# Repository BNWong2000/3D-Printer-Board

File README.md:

# 3D-Printer-Board
A custom, 3D printer controller, intended to run Klipper. All pcb source files were made in kiCAD. This project utilizes the stock kiCAD library for basic components (Resistors, Capacitors, Diodes, Inductors, Connectors, etc), and for the main chip (STM32F407IGT6). All other components were made as a custom library. 

#### Features:
* STM32F407IGT6 32 bit MCU
* 9 Silent Stepper Drivers (Trinamic TMC 2209 with UART control)
* 8 Fan output FETs
   * Selectable Voltage for each fan using jumpers. (24V, 12V or 5v)
* 8 Heater output FETs (including 1 high power FET for heated beds and 1 high power FET for heated chamber)
* High power step down converter to 5v (max 5A)
   * This is enough to power the raspberry pi (which only needs 3A at 5v) and several fans without an external power supply
* 12v step down converter for other peripherals.
* Fused inputs and outputs.

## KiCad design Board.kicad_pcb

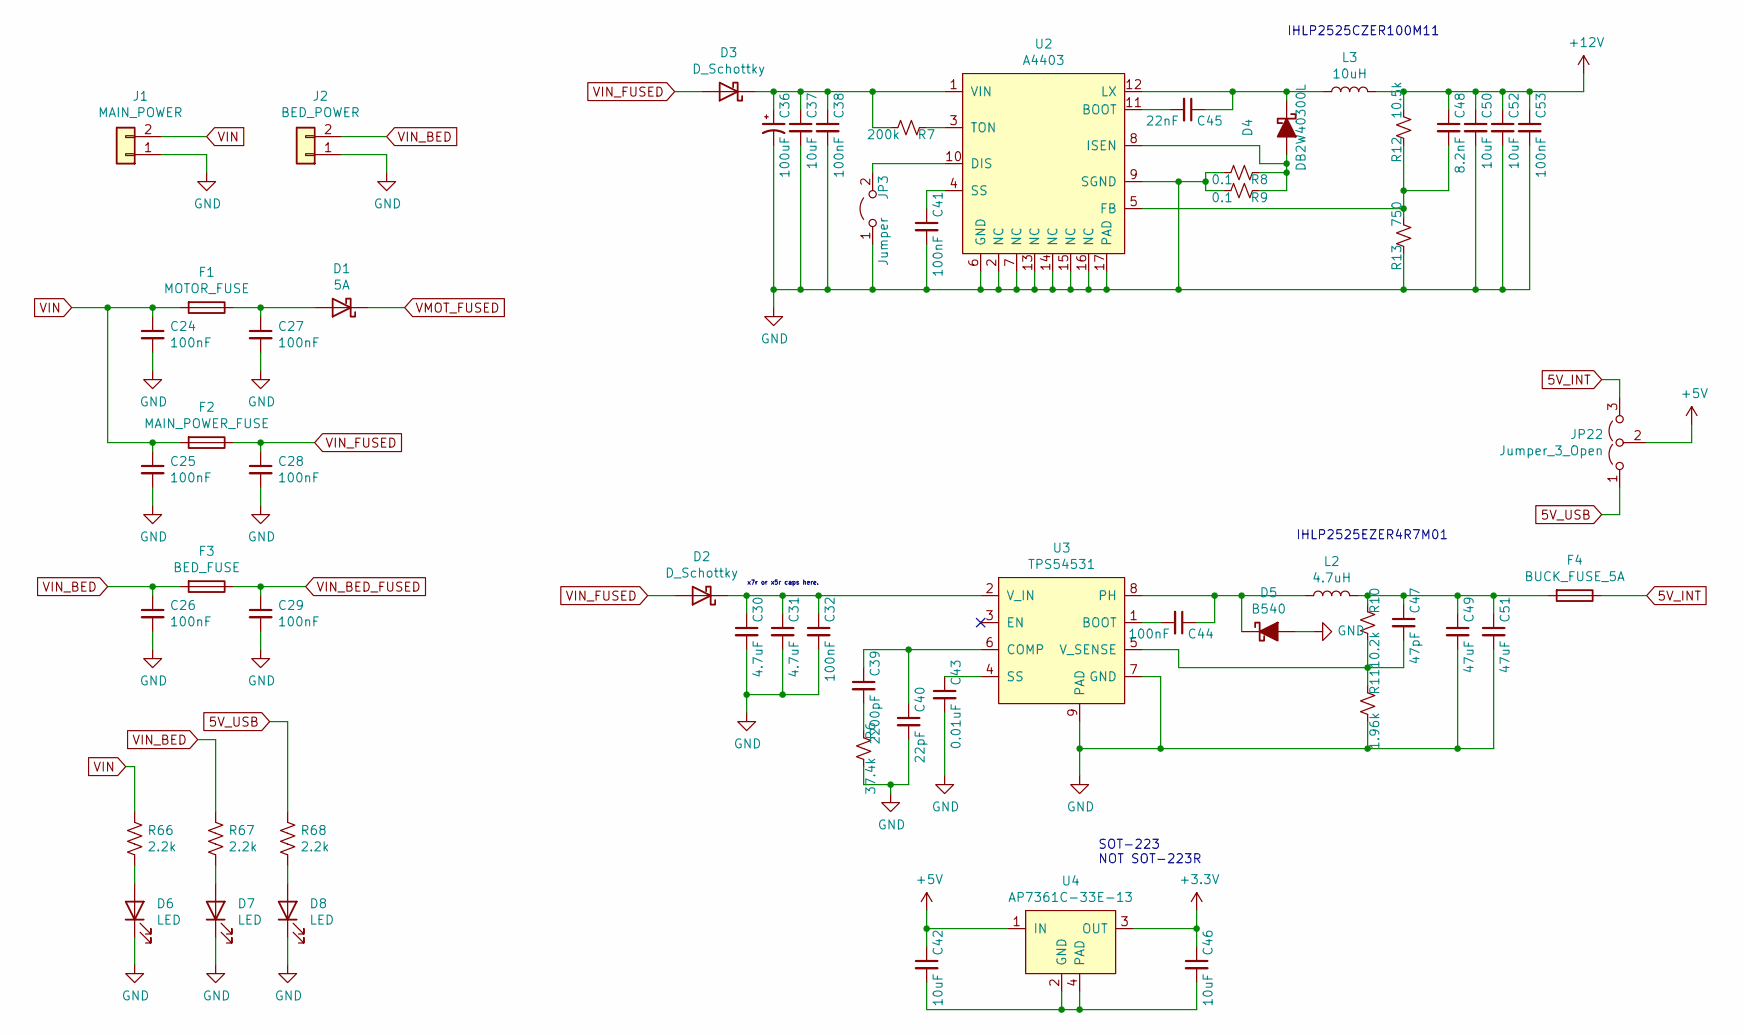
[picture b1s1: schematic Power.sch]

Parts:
C24, C25, C26, C27, C28, C29, C32, C38, C41, C44, C53: 100nF; C_0603_1608Metric_Pad1.05x0.95mm_HandSolder
C30, C31: 4.7uF; C_0805_2012Metric_Pad1.15x1.40mm_HandSolder
C36: 100uF; CP_Elec_6.3x7.7
C37, C42, C46, C50, C52: 10uF; C_0805_2012Metric_Pad1.15x1.40mm_HandSolder
C39: 2200pF; C_0603_1608Metric_Pad1.05x0.95mm_HandSolder
C40: 22pF; C_0603_1608Metric_Pad1.05x0.95mm_HandSolder
C43: 0.01uF; C_0603_1608Metric_Pad1.05x0.95mm_HandSolder
C45: 22nF; C_0603_1608Metric_Pad1.05x0.95mm_HandSolder
C47: 47pF; C_0603_1608Metric_Pad1.05x0.95mm_HandSolder
C48: 8.2nF; C_0603_1608Metric_Pad1.05x0.95mm_HandSolder
C49, C51: 47uF; C_0603_1608Metric_Pad1.05x0.95mm_HandSolder
D1: 5A; D_SMA_Handsoldering
D2, D3: D_Schottky; D_SOD-123F
D4: DB2W40300L; D_SOD-123F
D5: B540; D_SMC_Handsoldering
D6, D7, D8: LED; LED_0603_1608Metric_Pad1.05x0.95mm_HandSolder
F1: MOTOR_FUSE; Fuseholder_Blade_Mini_Keystone_3568
F2: MAIN_POWER_FUSE; Fuseholder_Blade_Mini_Keystone_3568
F3: BED_FUSE; Fuseholder_Blade_Mini_Keystone_3568
F4: BUCK_FUSE_5A; Fuseholder_Blade_Mini_Keystone_3568
J1: MAIN_POWER; TerminalBlock_Dinkle_DT-55-B01X-02_P10.00mm
J2: BED_POWER; TerminalBlock_Dinkle_DT-55-B01X-02_P10.00mm
JP3: Jumper; PinHeader_1x02_P2.54mm_Vertical
JP22: Jumper_3_Open; PinHeader_1x03_P2.54mm_Vertical
L2: 4.7uH; L_Vishay_IHLP-2525
L3: 10uH; L_Vishay_IHLP-2525
R6: 37.4k; R_0603_1608Metric_Pad1.05x0.95mm_HandSolder
R7: 200k; R_0603_1608Metric_Pad1.05x0.95mm_HandSolder
R8, R9: 0.1; R_1206_3216Metric_Pad1.42x1.75mm_HandSolder
R10: 10.2k; R_0603_1608Metric_Pad1.05x0.95mm_HandSolder
R11: 1.96k; R_0603_1608Metric_Pad1.05x0.95mm_HandSolder
R12: 10.5k; R_0603_1608Metric_Pad1.05x0.95mm_HandSolder
R13: 750; R_0603_1608Metric_Pad1.05x0.95mm_HandSolder
R66, R67, R68: 2.2k; R_0603_1608Metric_Pad1.05x0.95mm_HandSolder
U2: A4403; QFN-16-1EP_4x4mm_P0.65mm_EP2.7x2.7mm_ThermalVias
U3: TPS54531; TI_SO-PowerPAD-8_ThermalVias
U4: AP7361C-33E-13; SOT-223

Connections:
5V_INT: F4.1, JP22.3 (B)
5V_USB: JP22.1 (A), R68.1; also elsewhere on the board
+3V3: C46.1, U4.3 (OUT); also elsewhere on the board
+5V: C42.1, JP22.2 (C), U4.1 (IN); also elsewhere on the board
+12V: C48.1, C50.1, C52.1, C53.1, L3.2, R12.2; also elsewhere on the board
GND: C24.2, C25.2, C26.2, C27.2, C28.2, C29.2, C30.2, C31.2, C32.2, C36.2, C37.2, C38.2, C40.2, C41.2, C43.2, C49.2, C50.2, C51.2, C52.2, C53.2, D5.2 (A), D6.1 (K), D7.1 (K), D8.1 (K), J1.1, J2.1, JP3.1 (A), R6.2, R8.2, R9.2, R11.2, R13.1, U2.2 (NC), U2.6 (GND), U2.7 (NC), U2.9 (SGND), U2.13 (NC), U2.14 (NC), U2.15 (NC), U2.16 (NC), U2.17 (PAD), U3.7 (GND), U3.9 (PAD); also elsewhere on the board
unnamed: C27.1, D1.2 (A), F1.1
unnamed: C30.1, C31.1, C32.1, D2.1 (K), U3.2 (V_IN)
unnamed: C36.1, C37.1, C38.1, D3.1 (K), R7.2, U2.1 (VIN)
unnamed: C39.1, C40.1, U3.6 (COMP)
unnamed: C39.2, R6.1
unnamed: C41.1, U2.4 (SS)
unnamed: C42.2, C46.2, U4.2 (GND), U4.4 (PAD)
unnamed: C43.1, U3.4 (SS)
unnamed: C44.1, D5.1 (K), L2.1, U3.8 (PH)
unnamed: C44.2, U3.1 (BOOT)
unnamed: C45.1, D4.1 (K), L3.1, U2.12 (LX)
unnamed: C45.2, U2.11 (BOOT)
unnamed: C47.1, C49.1, C51.1, F4.2, L2.2, R10.1
unnamed: C47.2, R10.2, R11.1, U3.5 (V_SENSE)
unnamed: C48.2, R12.1, R13.2, U2.5 (FB)
unnamed: D4.2 (A), R8.1, R9.1, U2.8 (ISEN)
unnamed: D6.2 (A), R66.2
unnamed: D7.2 (A), R67.2
unnamed: D8.2 (A), R68.2
unnamed: JP3.2 (B), U2.10 (DIS)
unnamed: R7.1, U2.3 (TON)
VIN: C24.1, C25.1, F1.2, F2.2, J1.2, R66.1
VIN_BED: C26.1, F3.2, J2.2, R67.1
VIN_BED_FUSED: C29.1, F3.1; also elsewhere on the board
VIN_FUSED: C28.1, D2.2 (A), D3.2 (A), F2.1; also elsewhere on the board
VMOT_FUSED: D1.1 (K); also elsewhere on the board

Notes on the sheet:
x7r or x5r caps here.
IHLP2525CZER100M11
IHLP2525EZER4R7M01
SOT-223 NOT SOT-223R

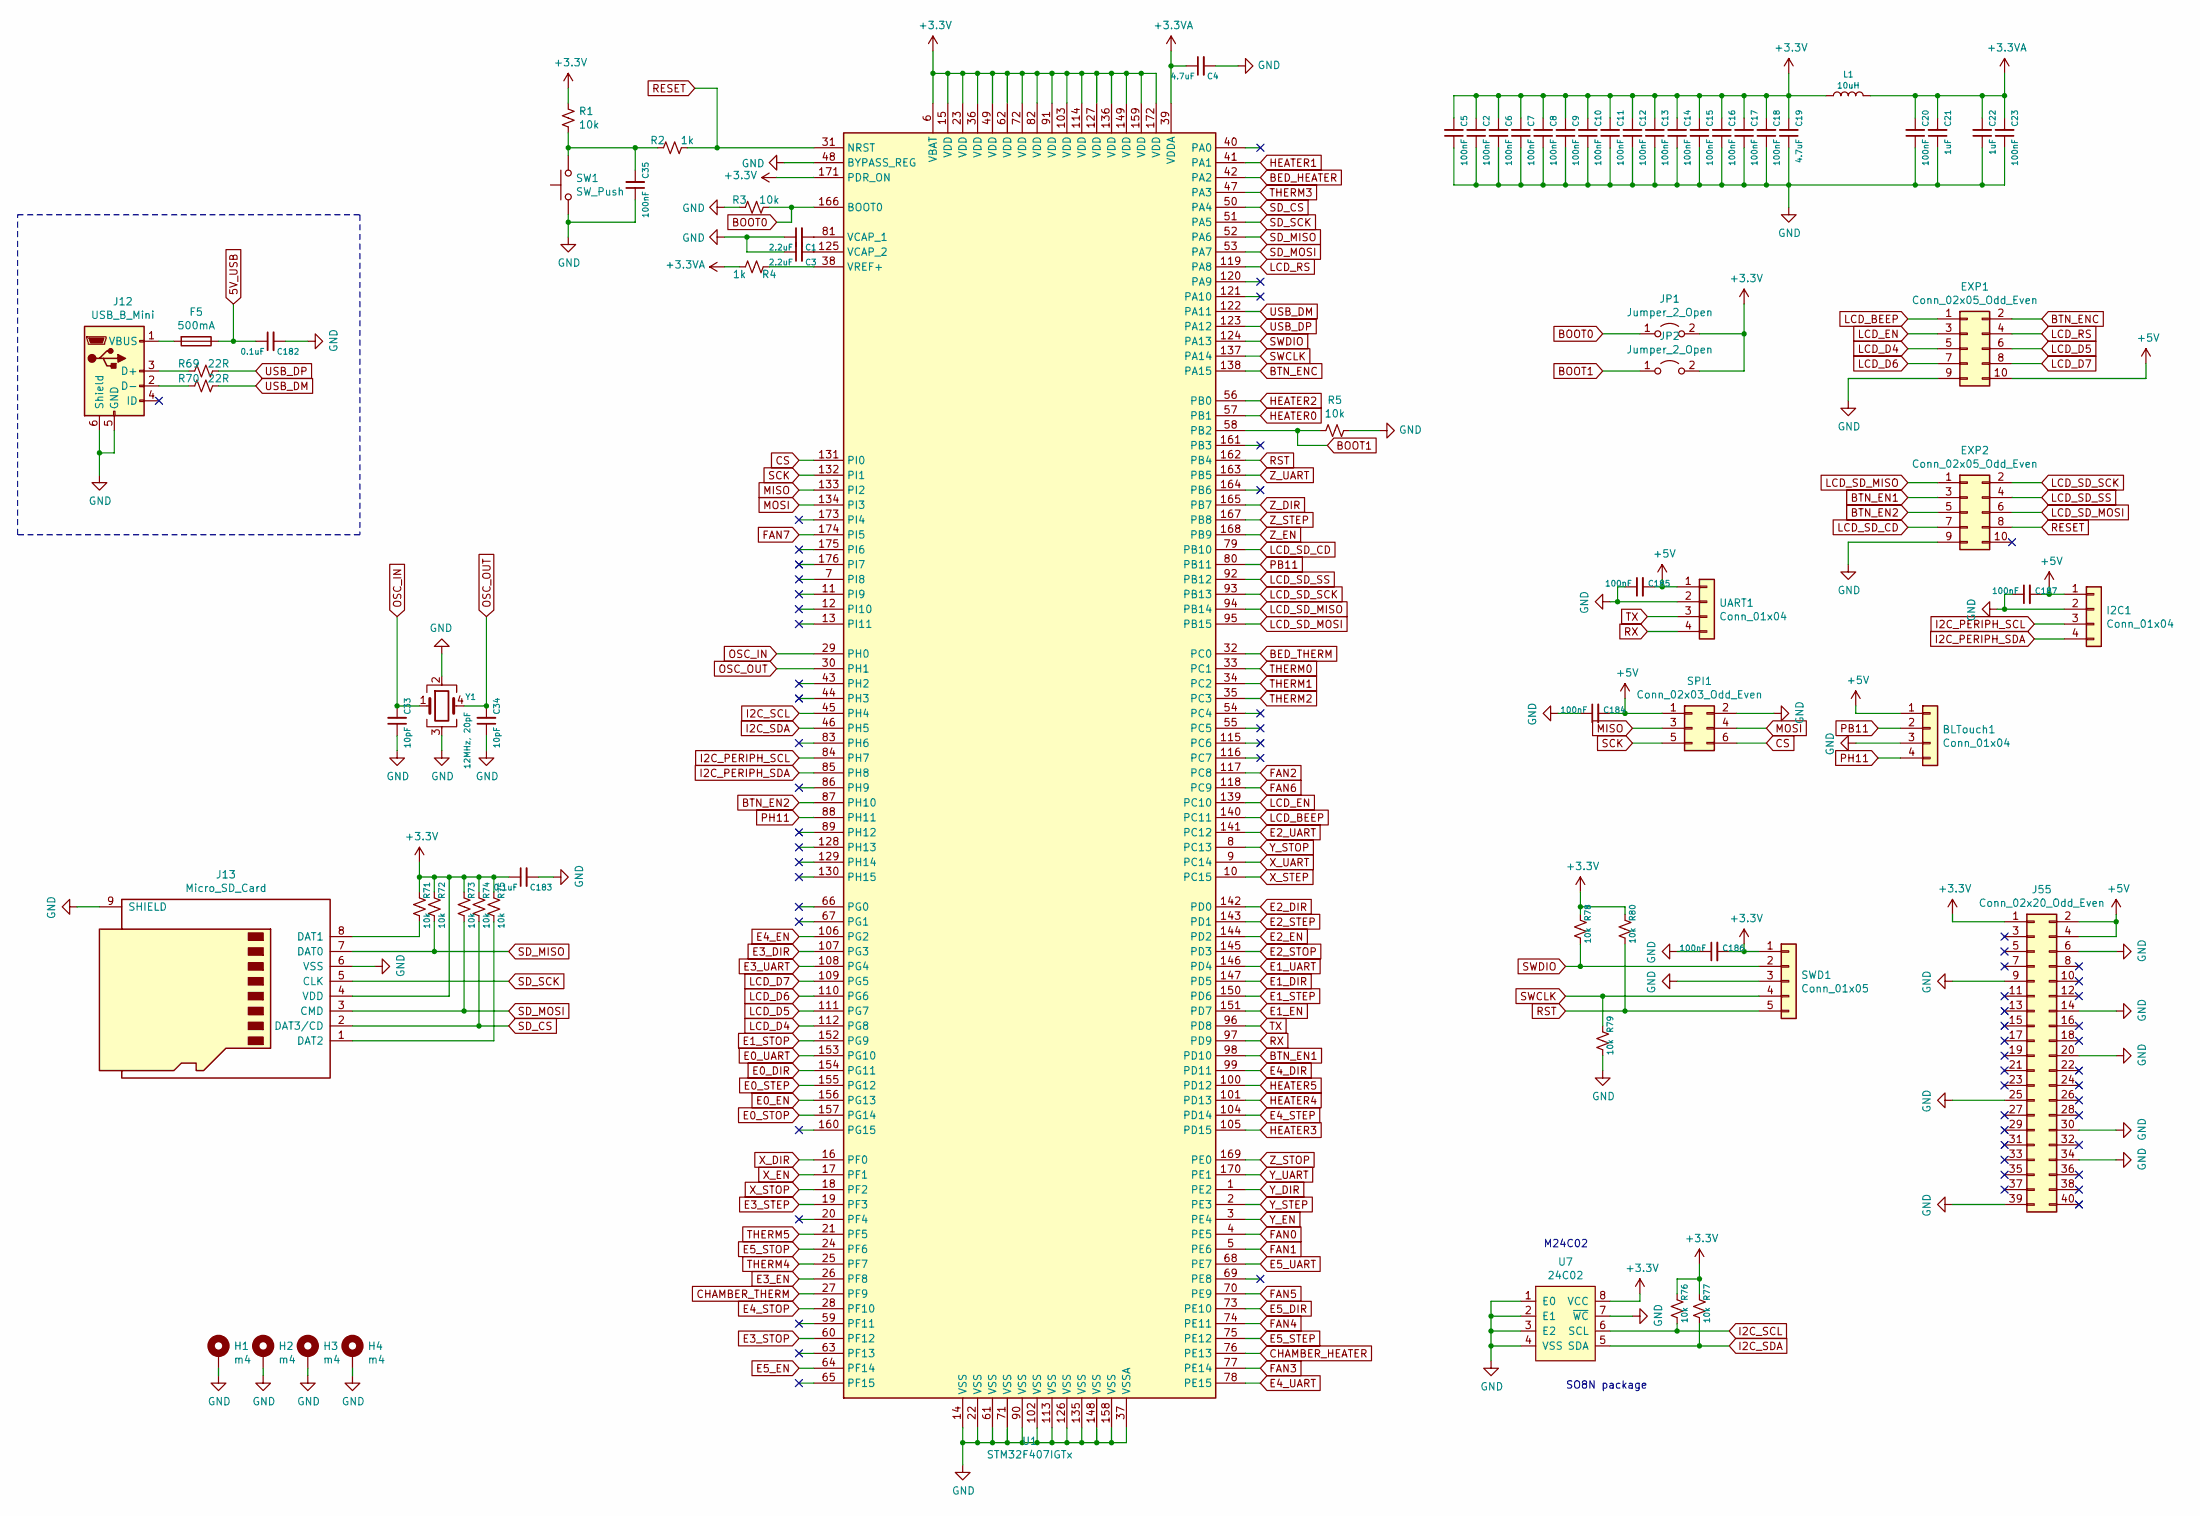
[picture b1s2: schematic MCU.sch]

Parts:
BLTouch1: Conn_01x04; PinHeader_1x04_P2.54mm_Vertical
C1, C3: 2.2uF; C_0603_1608Metric_Pad1.05x0.95mm_HandSolder
C2, C5, C6, C7, C8, C9, C10, C11, C12, C13, C14, C15, C16, C17, C18, C20, C23, C35, C184, C185, C186, C187: 100nF; C_0603_1608Metric_Pad1.05x0.95mm_HandSolder
C4, C19: 4.7uF; C_0805_2012Metric_Pad1.15x1.40mm_HandSolder
C21, C22: 1uF; C_0603_1608Metric_Pad1.05x0.95mm_HandSolder
C33, C34: 10pF; C_0603_1608Metric_Pad1.05x0.95mm_HandSolder
C182, C183: 0.1uF; C_0603_1608Metric_Pad1.05x0.95mm_HandSolder
EXP1, EXP2: Conn_02x05_Odd_Even; PinHeader_2x05_P2.54mm_Vertical
F5: 500mA; Fuse_1206_3216Metric_Pad1.42x1.75mm_HandSolder
H1, H2, H3, H4: m4; MountingHole_4.3mm_M4_Pad_Via
I2C1: Conn_01x04; PinHeader_1x04_P2.54mm_Vertical
J12: USB_B_Mini; USB_Mini-B_Wuerth_65100516121_Horizontal
J13: Micro_SD_Card; microSD_HC_Wuerth_693072010801
J55: Conn_02x20_Odd_Even; PinHeader_2x20_P2.54mm_Vertical
JP1, JP2: Jumper_2_Open; PinHeader_1x02_P2.54mm_Vertical
L1: 10uH; L_0603_1608Metric_Pad1.05x0.95mm_HandSolder
R1, R3, R5, R71, R72, R73, R74, R75, R76, R77, R78, R79, R80: 10k; R_0603_1608Metric_Pad1.05x0.95mm_HandSolder
R2, R4: 1k; R_0603_1608Metric_Pad1.05x0.95mm_HandSolder
R69, R70: 22R; R_0603_1608Metric_Pad1.05x0.95mm_HandSolder
SPI1: Conn_02x03_Odd_Even; PinHeader_2x03_P2.54mm_Vertical
SW1: SW_Push; SW_Push_1P1T_NO_6x6mm_H9.5mm
SWD1: Conn_01x05; PinHeader_1x05_P2.54mm_Vertical
U1: STM32F407IGTx; LQFP-176_24x24mm_P0.5mm
U7: 24C02; SO-8_3.9x4.9mm_P1.27mm
UART1: Conn_01x04; PinHeader_1x04_P2.54mm_Vertical
Y1: 12MHz, 20pF; Crystal_SMD_EuroQuartz_MJ-4Pin_5.0x3.2mm_HandSoldering

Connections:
5V_USB: C182.1, F5.1; also elsewhere on the board
+3.3VA: C4.1, C20.2, C21.2, C22.2, C23.2, L1.2, R4.2, U1.39 (VDDA); also elsewhere on the board
+3V3: C2.2, C5.2, C6.2, C7.2, C8.2, C9.2, C10.2, C11.2, C12.2, C13.2, C14.2, C15.2, C16.2, C17.2, C18.2, C19.2, C183.1, C186.2, J13.4 (VDD), J55.1, JP1.2 (B), JP2.2 (B), L1.1, R1.1, R71.1, R72.1, R73.1, R74.1, R75.1, R76.1, R77.1, R78.1, R80.1, SWD1.1, U1.6 (VBAT), U1.15 (VDD), U1.23 (VDD), U1.36 (VDD), U1.49 (VDD), U1.62 (VDD), U1.72 (VDD), U1.82 (VDD), U1.91 (VDD), U1.103 (VDD), U1.114 (VDD), U1.127 (VDD), U1.136 (VDD), U1.149 (VDD), U1.159 (VDD), U1.171 (PDR_ON), U1.172 (VDD), U7.8 (VCC); also elsewhere on the board
+5V: BLTouch1.1, C184.2, C185.2, C187.2, EXP1.10, I2C1.1, J55.2, J55.4, SPI1.1, UART1.1; also elsewhere on the board
BED_HEATER: U1.42 (PA2); also elsewhere on the board
BED_THERM: U1.32 (PC0); also elsewhere on the board
BOOT0: JP1.1 (A), R3.1, U1.166 (BOOT0)
BOOT1: JP2.1 (A), R5.2, U1.58 (PB2)
BTN_EN1: EXP2.3, U1.98 (PD10)
BTN_EN2: EXP2.5, U1.87 (PH10)
BTN_ENC: EXP1.2, U1.138 (PA15)
CHAMBER_HEATER: U1.76 (PE13); also elsewhere on the board
CHAMBER_THERM: U1.27 (PF9); also elsewhere on the board
CS: SPI1.6, U1.131 (PI0)
E0_DIR: U1.154 (PG11); also elsewhere on the board
E0_EN: U1.156 (PG13); also elsewhere on the board
E0_STEP: U1.155 (PG12); also elsewhere on the board
E0_STOP: U1.157 (PG14); also elsewhere on the board
E0_UART: U1.153 (PG10); also elsewhere on the board
E1_DIR: U1.147 (PD5); also elsewhere on the board
E1_EN: U1.151 (PD7); also elsewhere on the board
E1_STEP: U1.150 (PD6); also elsewhere on the board
E1_STOP: U1.152 (PG9); also elsewhere on the board
E1_UART: U1.146 (PD4); also elsewhere on the board
E2_DIR: U1.142 (PD0); also elsewhere on the board
E2_EN: U1.144 (PD2); also elsewhere on the board
E2_STEP: U1.143 (PD1); also elsewhere on the board
E2_STOP: U1.145 (PD3); also elsewhere on the board
E2_UART: U1.141 (PC12); also elsewhere on the board
E3_DIR: U1.107 (PG3); also elsewhere on the board
E3_EN: U1.26 (PF8); also elsewhere on the board
E3_STEP: U1.19 (PF3); also elsewhere on the board
E3_STOP: U1.60 (PF12); also elsewhere on the board
E3_UART: U1.108 (PG4); also elsewhere on the board
E4_DIR: U1.99 (PD11); also elsewhere on the board
E4_EN: U1.106 (PG2); also elsewhere on the board
E4_STEP: U1.104 (PD14); also elsewhere on the board
E4_STOP: U1.28 (PF10); also elsewhere on the board
E4_UART: U1.78 (PE15); also elsewhere on the board
E5_DIR: U1.73 (PE10); also elsewhere on the board
E5_EN: U1.64 (PF14); also elsewhere on the board
E5_STEP: U1.75 (PE12); also elsewhere on the board
E5_STOP: U1.24 (PF6); also elsewhere on the board
E5_UART: U1.68 (PE7); also elsewhere on the board
FAN0: U1.4 (PE5); also elsewhere on the board
FAN1: U1.5 (PE6); also elsewhere on the board
FAN2: U1.117 (PC8); also elsewhere on the board
FAN3: U1.77 (PE14); also elsewhere on the board
FAN4: U1.74 (PE11); also elsewhere on the board
FAN5: U1.70 (PE9); also elsewhere on the board
FAN6: U1.118 (PC9); also elsewhere on the board
FAN7: U1.174 (PI5); also elsewhere on the board
GND: BLTouch1.3, C1.1, C2.1, C3.1, C4.2, C5.1, C6.1, C7.1, C8.1, C9.1, C10.1, C11.1, C12.1, C13.1, C14.1, C15.1, C16.1, C17.1, C18.1, C19.1, C20.1, C21.1, C22.1, C23.1, C33.1, C34.1, C35.1, C182.2, C183.2, C184.1, C185.1, C186.1, C187.1, EXP1.9, EXP2.9, H1.1, H2.1, H3.1, H4.1, I2C1.2, J12.5 (GND), J12.6 (Shield), J13.6 (VSS), J13.9 (SHIELD), J55.6, J55.9, J55.14, J55.20, J55.25, J55.30, J55.34, J55.39, R3.2, R5.1, R79.2, SPI1.2, SW1.1, SWD1.3, U1.14 (VSS), U1.22 (VSS), U1.37 (VSSA), U1.48 (BYPASS_REG), U1.61 (VSS), U1.71 (VSS), U1.90 (VSS), U1.102 (VSS), U1.113 (VSS), U1.126 (VSS), U1.135 (VSS), U1.148 (VSS), U1.158 (VSS), U7.1 (E0), U7.2 (E1), U7.3 (E2), U7.4 (VSS), U7.7 (~WC), UART1.2, Y1.2, Y1.3; also elsewhere on the board
HEATER0: U1.57 (PB1); also elsewhere on the board
HEATER1: U1.41 (PA1); also elsewhere on the board
HEATER2: U1.56 (PB0); also elsewhere on the board
HEATER3: U1.105 (PD15); also elsewhere on the board
HEATER4: U1.101 (PD13); also elsewhere on the board
HEATER5: U1.100 (PD12); also elsewhere on the board
I2C_PERIPH_SCL: I2C1.3, U1.84 (PH7)
I2C_PERIPH_SDA: I2C1.4, U1.85 (PH8)
I2C_SCL: R76.2, U1.45 (PH4), U7.6 (SCL)
I2C_SDA: R77.2, U1.46 (PH5), U7.5 (SDA)
LCD_BEEP: EXP1.1, U1.140 (PC11)
LCD_D4: EXP1.5, U1.112 (PG8)
LCD_D5: EXP1.6, U1.111 (PG7)
LCD_D6: EXP1.7, U1.110 (PG6)
LCD_D7: EXP1.8, U1.109 (PG5)
LCD_EN: EXP1.3, U1.139 (PC10)
LCD_RS: EXP1.4, U1.119 (PA8)
LCD_SD_CD: EXP2.7, U1.79 (PB10)
LCD_SD_MISO: EXP2.1, U1.94 (PB14)
LCD_SD_MOSI: EXP2.6, U1.95 (PB15)
LCD_SD_SCK: EXP2.2, U1.93 (PB13)
LCD_SD_SS: EXP2.4, U1.92 (PB12)
MISO: SPI1.3, U1.133 (PI2)
MOSI: SPI1.4, U1.134 (PI3)
unnamed: C1.2, U1.81 (VCAP_1)
unnamed: C3.2, U1.125 (VCAP_2)
unnamed: C35.2, R1.2, R2.2, SW1.2
unnamed: F5.2, J12.1 (VBUS)
unnamed: J12.2 (D-), R70.2
unnamed: J12.3 (D+), R69.2
unnamed: J13.1 (DAT2), R75.2
unnamed: J13.8 (DAT1), R71.2
unnamed: R4.1, U1.38 (VREF+)
OSC_IN: C33.2, U1.29 (PH0), Y1.1
OSC_OUT: C34.2, U1.30 (PH1), Y1.4
PB11: BLTouch1.2, U1.80 (PB11)
PH11: BLTouch1.4, U1.88 (PH11)
RESET: EXP2.8, R2.1, U1.31 (NRST)
RST: R80.2, SWD1.5, U1.162 (PB4)
RX: U1.97 (PD9), UART1.4
SCK: SPI1.5, U1.132 (PI1)
SD_CS: J13.2 (DAT3/CD), R74.2, U1.50 (PA4)
SD_MISO: J13.7 (DAT0), R72.2, U1.52 (PA6)
SD_MOSI: J13.3 (CMD), R73.2, U1.53 (PA7)
SD_SCK: J13.5 (CLK), U1.51 (PA5)
SWCLK: R79.1, SWD1.4, U1.137 (PA14)
SWDIO: R78.2, SWD1.2, U1.124 (PA13)
THERM0: U1.33 (PC1); also elsewhere on the board
THERM1: U1.34 (PC2); also elsewhere on the board
THERM2: U1.35 (PC3); also elsewhere on the board
THERM3: U1.47 (PA3); also elsewhere on the board
THERM4: U1.25 (PF7); also elsewhere on the board
THERM5: U1.21 (PF5); also elsewhere on the board
TX: U1.96 (PD8), UART1.3
USB_DM: R70.1, U1.122 (PA11)
USB_DP: R69.1, U1.123 (PA12)
X_DIR: U1.16 (PF0); also elsewhere on the board
X_EN: U1.17 (PF1); also elsewhere on the board
X_STEP: U1.10 (PC15); also elsewhere on the board
X_STOP: U1.18 (PF2); also elsewhere on the board
X_UART: U1.9 (PC14); also elsewhere on the board
Y_DIR: U1.1 (PE2); also elsewhere on the board
Y_EN: U1.3 (PE4); also elsewhere on the board
Y_STEP: U1.2 (PE3); also elsewhere on the board
Y_STOP: U1.8 (PC13); also elsewhere on the board
Y_UART: U1.170 (PE1); also elsewhere on the board
Z_DIR: U1.165 (PB7); also elsewhere on the board
Z_EN: U1.168 (PB9); also elsewhere on the board
Z_STEP: U1.167 (PB8); also elsewhere on the board
Z_STOP: U1.169 (PE0); also elsewhere on the board
Z_UART: U1.163 (PB5); also elsewhere on the board

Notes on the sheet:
M24C02
SO8N package

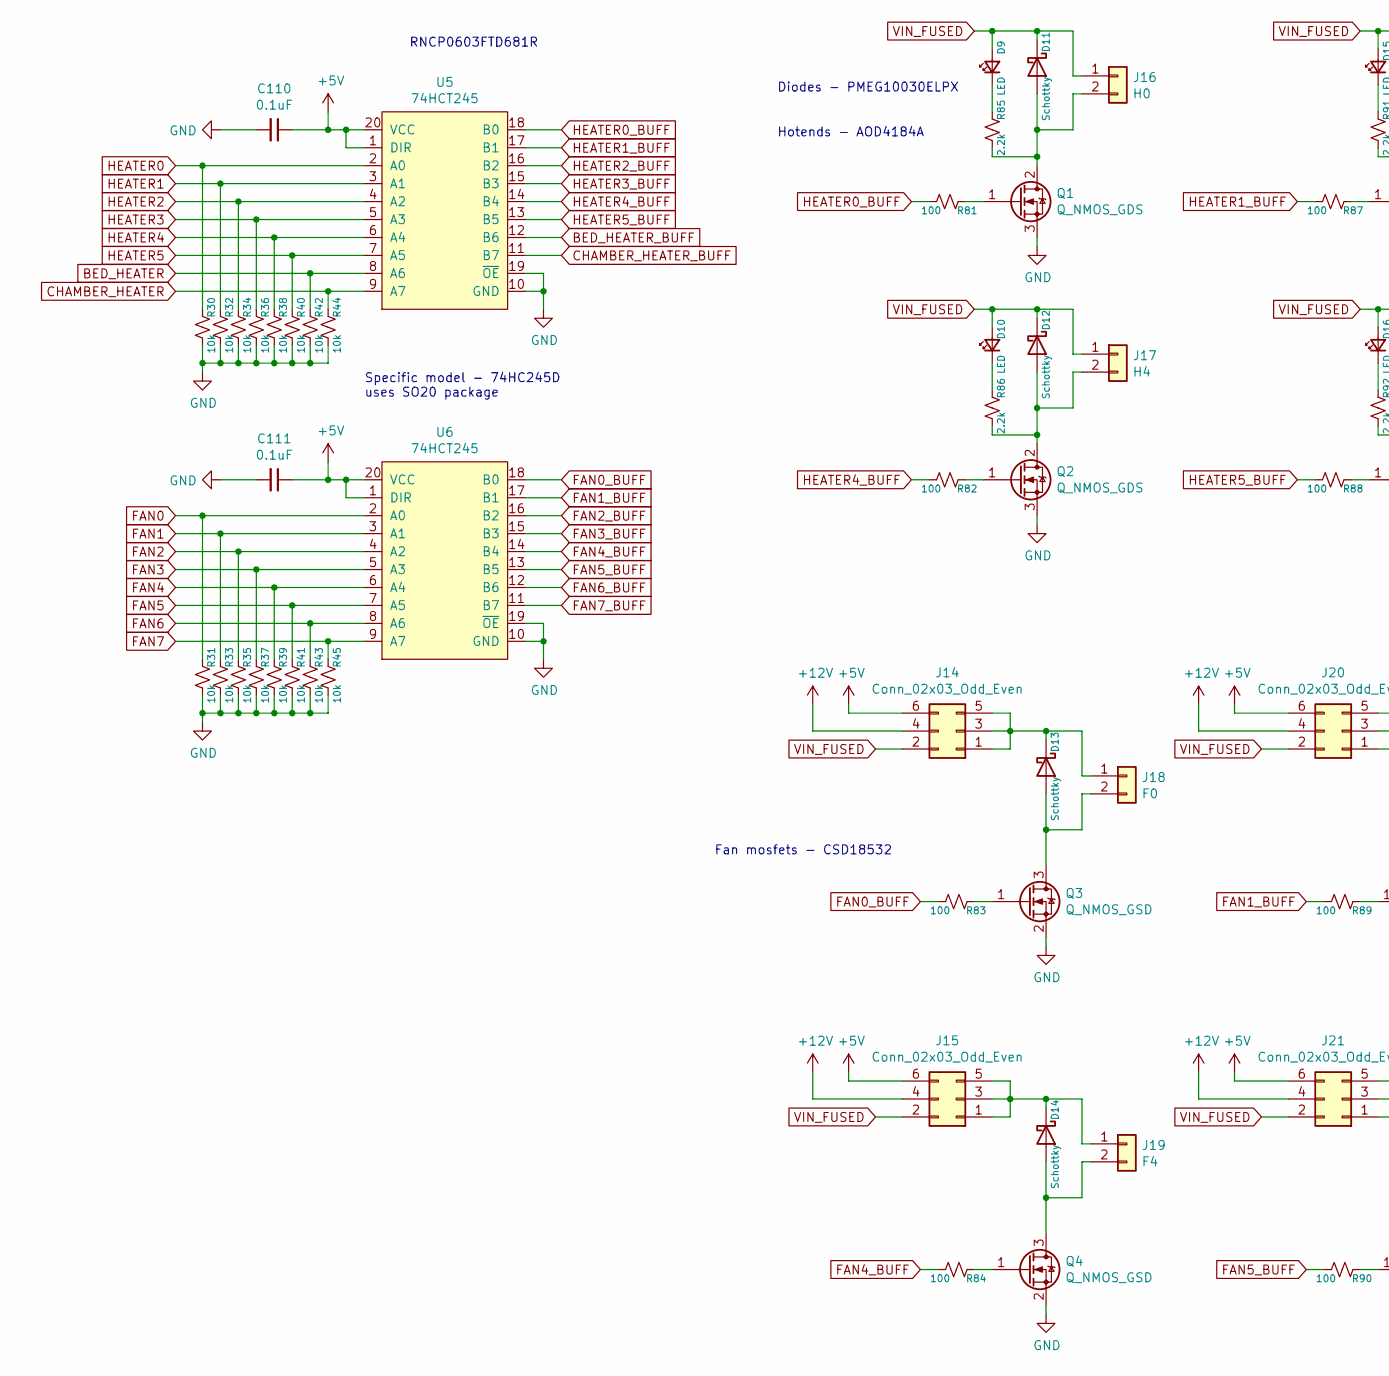
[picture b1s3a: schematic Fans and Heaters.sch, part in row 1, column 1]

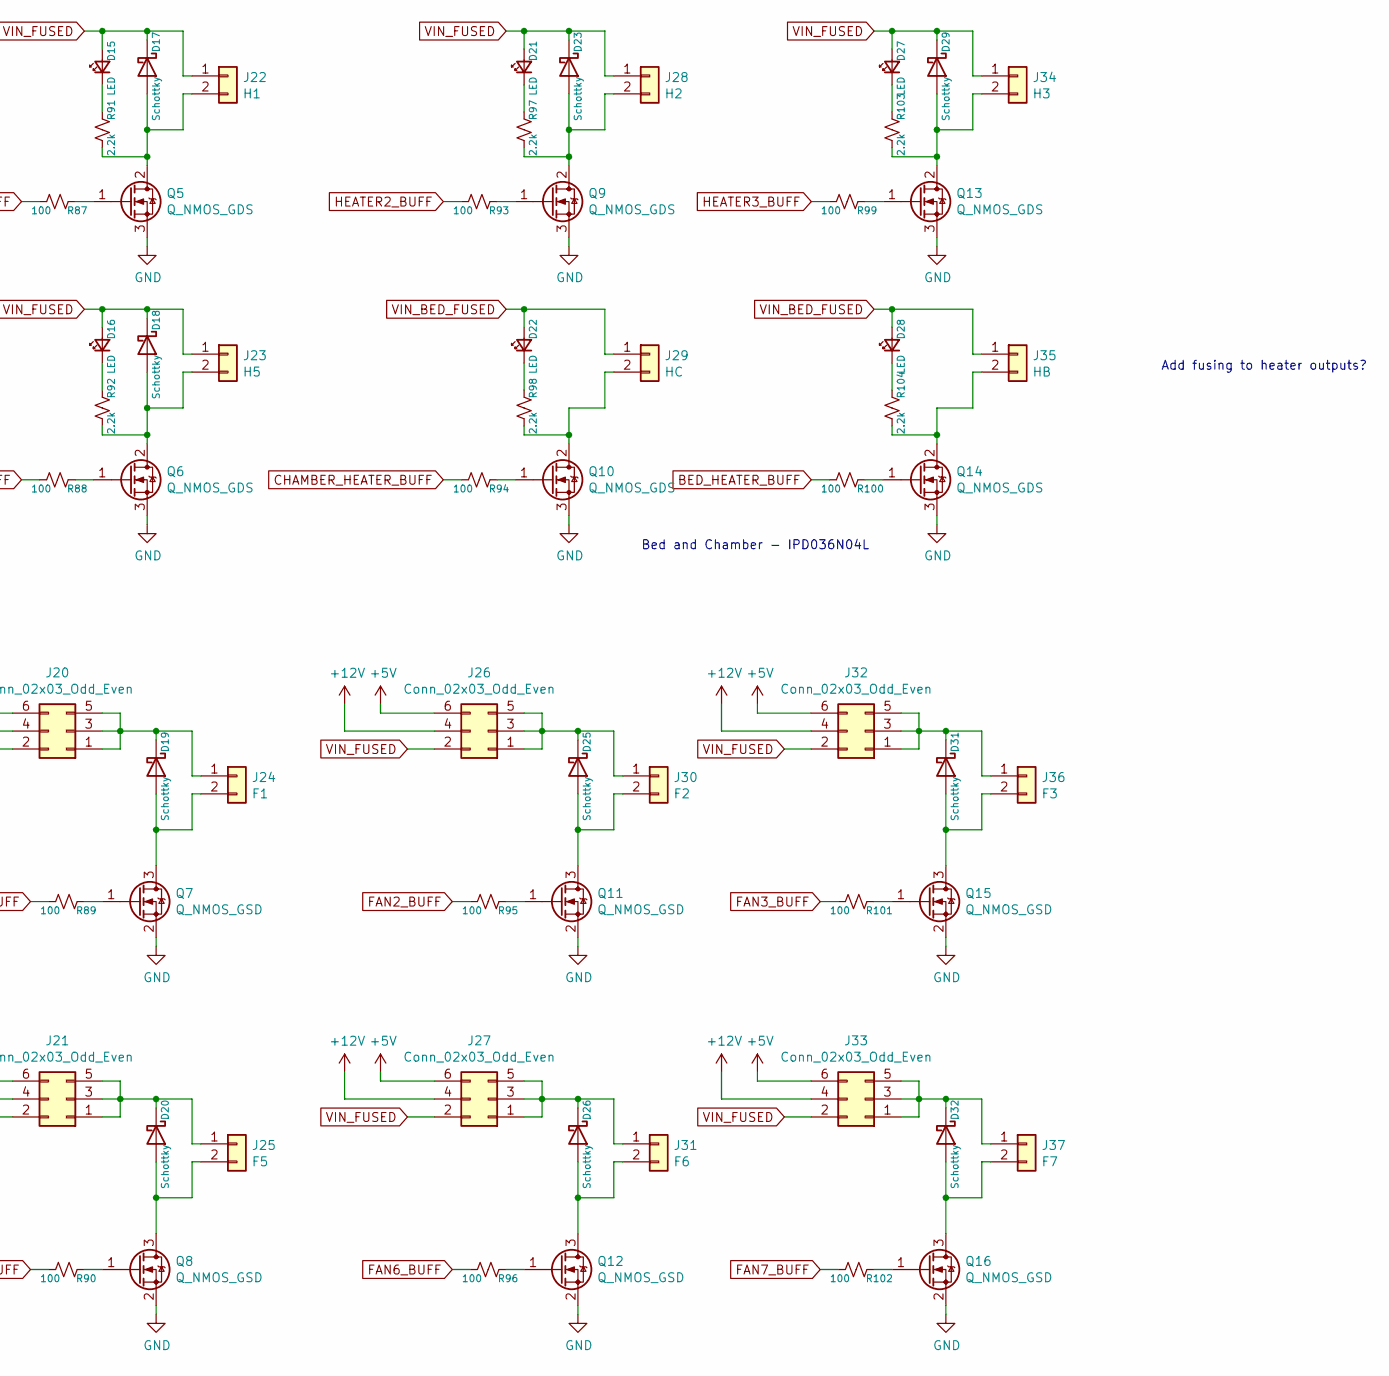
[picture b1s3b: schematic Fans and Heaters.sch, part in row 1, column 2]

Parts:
C110, C111: 0.1uF; C_0603_1608Metric_Pad1.05x0.95mm_HandSolder
D9, D10, D15, D16, D21, D22, D27, D28: LED; LED_0603_1608Metric_Pad1.05x0.95mm_HandSolder
D11, D12, D13, D14, D17, D18, D19, D20, D23, D25, D26, D29, D31, D32: Schottky; D_SOD-128
J14, J15, J20, J21, J26, J27, J32, J33: Conn_02x03_Odd_Even; PinHeader_2x03_P2.54mm_Vertical
J16: H0; TerminalBlock_Phoenix_MKDS-1,5-2_1x02_P5.00mm_Horizontal
J17: H4; TerminalBlock_Phoenix_MKDS-1,5-2_1x02_P5.00mm_Horizontal
J18: F0; Molex_KK-254_AE-6410-02A_1x02_P2.54mm_Vertical
J19: F4; Molex_KK-254_AE-6410-02A_1x02_P2.54mm_Vertical
J22: H1; TerminalBlock_Phoenix_MKDS-1,5-2_1x02_P5.00mm_Horizontal
J23: H5; TerminalBlock_Phoenix_MKDS-1,5-2_1x02_P5.00mm_Horizontal
J24: F1; Molex_KK-254_AE-6410-02A_1x02_P2.54mm_Vertical
J25: F5; Molex_KK-254_AE-6410-02A_1x02_P2.54mm_Vertical
J28: H2; TerminalBlock_Phoenix_MKDS-1,5-2_1x02_P5.00mm_Horizontal
J29: HC; TerminalBlock_Dinkle_DT-55-B01X-02_P10.00mm
J30: F2; Molex_KK-254_AE-6410-02A_1x02_P2.54mm_Vertical
J31: F6; Molex_KK-254_AE-6410-02A_1x02_P2.54mm_Vertical
J34: H3; TerminalBlock_Phoenix_MKDS-1,5-2_1x02_P5.00mm_Horizontal
J35: HB; TerminalBlock_Dinkle_DT-55-B01X-02_P10.00mm
J36: F3; Molex_KK-254_AE-6410-02A_1x02_P2.54mm_Vertical
J37: F7; Molex_KK-254_AE-6410-02A_1x02_P2.54mm_Vertical
Q1, Q2, Q5, Q6, Q9, Q10, Q13, Q14: Q_NMOS_GDS; TO-252-2
Q3, Q4, Q7, Q8, Q11, Q12, Q15, Q16: Q_NMOS_GSD; SOT-23_Handsoldering
R30, R31, R32, R33, R34, R35, R36, R37, R38, R39, R40, R41, R42, R43, R44, R45: 10k; R_0603_1608Metric_Pad1.05x0.95mm_HandSolder
R81, R82, R83, R84, R87, R88, R89, R90, R93, R94, R95, R96, R99, R100, R101, R102: 100; R_0603_1608Metric_Pad1.05x0.95mm_HandSolder
R85, R86, R91, R92, R97, R98, R103, R104: 2.2k; R_0603_1608Metric_Pad1.05x0.95mm_HandSolder
U5, U6: 74HCT245; SO-20_12.8x7.5mm_P1.27mm

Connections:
+5V: C110.1, C111.1, J14.6, J15.6, J20.6, J21.6, J26.6, J27.6, J32.6, J33.6, U5.1 (DIR), U5.20 (VCC), U6.1 (DIR), U6.20 (VCC); also elsewhere on the board
+12V: J14.4, J15.4, J20.4, J21.4, J26.4, J27.4, J32.4, J33.4; also elsewhere on the board
BED_HEATER: R42.1, U5.8 (A6); also elsewhere on the board
BED_HEATER_BUFF: R100.2, U5.12 (B6)
CHAMBER_HEATER: R44.1, U5.9 (A7); also elsewhere on the board
CHAMBER_HEATER_BUFF: R94.2, U5.11 (B7)
FAN0: R31.1, U6.2 (A0); also elsewhere on the board
FAN0_BUFF: R83.2, U6.18 (B0)
FAN1: R33.1, U6.3 (A1); also elsewhere on the board
FAN1_BUFF: R89.2, U6.17 (B1)
FAN2: R35.1, U6.4 (A2); also elsewhere on the board
FAN2_BUFF: R95.2, U6.16 (B2)
FAN3: R37.1, U6.5 (A3); also elsewhere on the board
FAN3_BUFF: R101.2, U6.15 (B3)
FAN4: R39.1, U6.6 (A4); also elsewhere on the board
FAN4_BUFF: R84.2, U6.14 (B4)
FAN5: R41.1, U6.7 (A5); also elsewhere on the board
FAN5_BUFF: R90.2, U6.13 (B5)
FAN6: R43.1, U6.8 (A6); also elsewhere on the board
FAN6_BUFF: R96.2, U6.12 (B6)
FAN7: R45.1, U6.9 (A7); also elsewhere on the board
FAN7_BUFF: R102.2, U6.11 (B7)
GND: C110.2, C111.2, Q1.3 (S), Q2.3 (S), Q3.2 (S), Q4.2 (S), Q5.3 (S), Q6.3 (S), Q7.2 (S), Q8.2 (S), Q9.3 (S), Q10.3 (S), Q11.2 (S), Q12.2 (S), Q13.3 (S), Q14.3 (S), Q15.2 (S), Q16.2 (S), R30.2, R31.2, R32.2, R33.2, R34.2, R35.2, R36.2, R37.2, R38.2, R39.2, R40.2, R41.2, R42.2, R43.2, R44.2, R45.2, U5.10 (GND), U5.19 (~OE), U6.10 (GND), U6.19 (~OE); also elsewhere on the board
HEATER0: R30.1, U5.2 (A0); also elsewhere on the board
HEATER0_BUFF: R81.2, U5.18 (B0)
HEATER1: R32.1, U5.3 (A1); also elsewhere on the board
HEATER1_BUFF: R87.2, U5.17 (B1)
HEATER2: R34.1, U5.4 (A2); also elsewhere on the board
HEATER2_BUFF: R93.2, U5.16 (B2)
HEATER3: R36.1, U5.5 (A3); also elsewhere on the board
HEATER3_BUFF: R99.2, U5.15 (B3)
HEATER4: R38.1, U5.6 (A4); also elsewhere on the board
HEATER4_BUFF: R82.2, U5.14 (B4)
HEATER5: R40.1, U5.7 (A5); also elsewhere on the board
HEATER5_BUFF: R88.2, U5.13 (B5)
unnamed: D9.1 (K), R85.1
unnamed: D10.1 (K), R86.1
unnamed: D11.2 (A), J16.2, Q1.2 (D), R85.2
unnamed: D12.2 (A), J17.2, Q2.2 (D), R86.2
unnamed: D13.1 (K), J14.1, J14.3, J14.5, J18.1
unnamed: D13.2 (A), J18.2, Q3.3 (D)
unnamed: D14.1 (K), J15.1, J15.3, J15.5, J19.1
unnamed: D14.2 (A), J19.2, Q4.3 (D)
unnamed: D15.1 (K), R91.1
unnamed: D16.1 (K), R92.1
unnamed: D17.2 (A), J22.2, Q5.2 (D), R91.2
unnamed: D18.2 (A), J23.2, Q6.2 (D), R92.2
unnamed: D19.1 (K), J20.1, J20.3, J20.5, J24.1
unnamed: D19.2 (A), J24.2, Q7.3 (D)
unnamed: D20.1 (K), J21.1, J21.3, J21.5, J25.1
unnamed: D20.2 (A), J25.2, Q8.3 (D)
unnamed: D21.1 (K), R97.1
unnamed: D22.1 (K), R98.1
unnamed: D23.2 (A), J28.2, Q9.2 (D), R97.2
unnamed: D25.1 (K), J26.1, J26.3, J26.5, J30.1
unnamed: D25.2 (A), J30.2, Q11.3 (D)
unnamed: D26.1 (K), J27.1, J27.3, J27.5, J31.1
unnamed: D26.2 (A), J31.2, Q12.3 (D)
unnamed: D27.1 (K), R103.1
unnamed: D28.1 (K), R104.1
unnamed: D29.2 (A), J34.2, Q13.2 (D), R103.2
unnamed: D31.1 (K), J32.1, J32.3, J32.5, J36.1
unnamed: D31.2 (A), J36.2, Q15.3 (D)
unnamed: D32.1 (K), J33.1, J33.3, J33.5, J37.1
unnamed: D32.2 (A), J37.2, Q16.3 (D)
unnamed: J29.2, Q10.2 (D), R98.2
unnamed: J35.2, Q14.2 (D), R104.2
unnamed: Q1.1 (G), R81.1
unnamed: Q2.1 (G), R82.1
unnamed: Q3.1 (G), R83.1
unnamed: Q4.1 (G), R84.1
unnamed: Q5.1 (G), R87.1
unnamed: Q6.1 (G), R88.1
unnamed: Q7.1 (G), R89.1
unnamed: Q8.1 (G), R90.1
unnamed: Q9.1 (G), R93.1
unnamed: Q10.1 (G), R94.1
unnamed: Q11.1 (G), R95.1
unnamed: Q12.1 (G), R96.1
unnamed: Q13.1 (G), R99.1
unnamed: Q14.1 (G), R100.1
unnamed: Q15.1 (G), R101.1
unnamed: Q16.1 (G), R102.1
VIN_BED_FUSED: D22.2 (A), D28.2 (A), J29.1, J35.1; also elsewhere on the board
VIN_FUSED: D9.2 (A), D10.2 (A), D11.1 (K), D12.1 (K), D15.2 (A), D16.2 (A), D17.1 (K), D18.1 (K), D21.2 (A), D23.1 (K), D27.2 (A), D29.1 (K), J14.2, J15.2, J16.1, J17.1, J20.2, J21.2, J22.1, J23.1, J26.2, J27.2, J28.1, J32.2, J33.2, J34.1; also elsewhere on the board

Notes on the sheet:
Add fusing to heater outputs?
Diodes - PMEG10030ELPX
RNCP0603FTD681R
Fan mosfets - CSD18532
Bed and Chamber - IPD036N04L
Hotends - AOD4184A
Specific model - 74HC245D uses SO20 package

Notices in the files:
Endstops.sch:
creativecommons.org/licenses/by/4.0
License: CC BY 4.0
